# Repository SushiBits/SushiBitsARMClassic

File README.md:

# SushiBits ARM Classic

ARM7TDMI-S in Arduino form factor.

## License

This is open source hardware licensed under [3-clause BSD license](LICENSE.md).

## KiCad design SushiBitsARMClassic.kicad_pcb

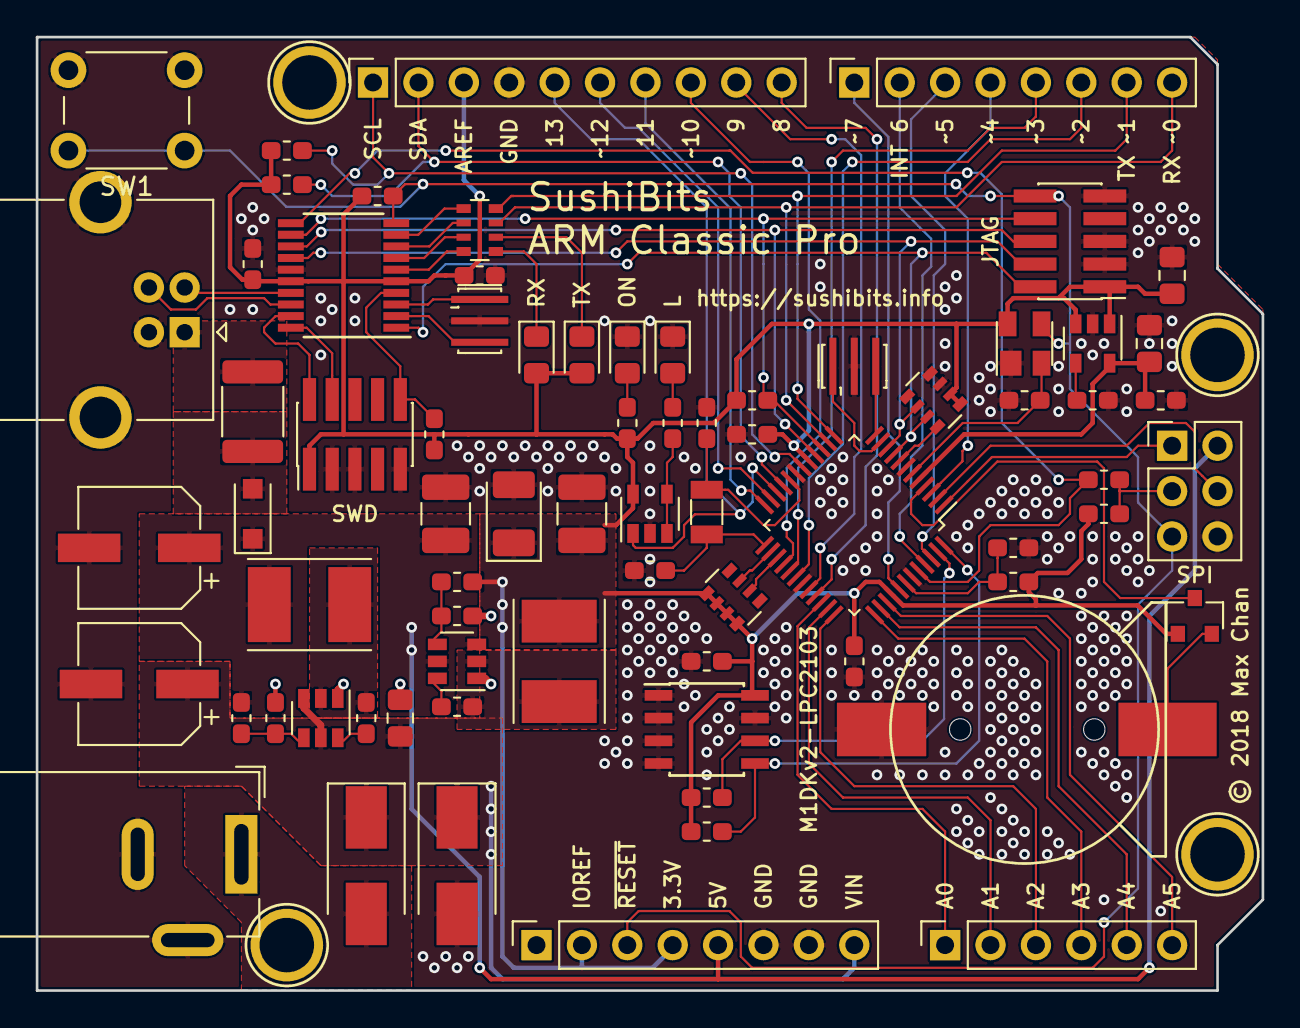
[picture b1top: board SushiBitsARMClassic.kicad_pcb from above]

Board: 2 copper layers, 68.6 x 53.3 mm, 77 parts (0 on the bottom side), 75 nets.

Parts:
BT1: CR1220; Battery_Holder_CR1220
C1, C2, C3, C4, C5, C12, C13, C14, C19, C20: 100n; C_0603_1608Metric_Pad1.05x0.95mm_HandSolder
C6, C7: 3p; C_0603_1608Metric_Pad1.05x0.95mm_HandSolder
C8: 100µ; CP_Elec_6.3x7.7
C9, C11, C15: 10µ; C_0805_2012Metric_Pad1.15x1.40mm_HandSolder
C10: 47µ; C_1210_3225Metric_Pad1.42x2.65mm_HandSolder
C16: 220µ; CP_Elec_6.3x5.3
C17: 220µ; CP_EIA-3528-12_Kemet-T_Pad1.50x2.35mm_HandSolder
C18: 47u; C_1210_3225Metric_Pad1.42x2.65mm_HandSolder
D1: L13; LED_0805_2012Metric_Pad1.15x1.40mm_HandSolder
D2: SK34; D_SMB_Handsoldering
D3: SMBJ15CA; D_SMB_Handsoldering
D4: BAT54C; SOT-23
D5: K34; D_SOD-123F
D6: Power; LED_0805_2012Metric_Pad1.15x1.40mm_HandSolder
D7: RX; LED_0805_2012Metric_Pad1.15x1.40mm_HandSolder
D8: TX; LED_0805_2012Metric_Pad1.15x1.40mm_HandSolder
F1: 1A; Fuse_1812_4532Metric_Pad1.30x3.40mm_HandSolder
J1: SPI; PinHeader_2x03_P2.54mm_Vertical
J2: JTAG; PinHeader_2x05_P1.27mm_Vertical_SMD
J3: DC12V; BarrelJack_Wuerth_6941xx301002
J4: USB_B; USB_B_OST_USB-B1HSxx_Horizontal
J5: Conn_ARM_JTAG_SWD_10; PinHeader_2x05_P1.27mm_Vertical_SMD
L1: 120; L_0603_1608Metric_Pad1.05x0.95mm_HandSolder
L2: 4.7µ; L_Taiyo-Yuden_NR-50xx_HandSoldering
L3: 2.2µ; L_Taiyo-Yuden_NR-50xx_HandSoldering
M1: LPC2103; LQFP-48_7x7mm_P0.5mm
P1: Power; PinSocket_1x08_P2.54mm_Vertical
P2: Analog; PinSocket_1x06_P2.54mm_Vertical
P3: Digital; PinSocket_1x10_P2.54mm_Vertical
P4: Digital; PinSocket_1x08_P2.54mm_Vertical
P5, P6, P7, P8: CONN_01X01; Arduino_1pin
R1, R2, R9, R12, R16: 10k; R_0603_1608Metric_Pad1.05x0.95mm_HandSolder
R3, R4, R5, R6, R8: 4.7k; R_0603_1608Metric_Pad1.05x0.95mm_HandSolder
R7, R15: 510; R_0603_1608Metric_Pad1.05x0.95mm_HandSolder
R10: R; R_0603_1608Metric_Pad1.05x0.95mm_HandSolder
R11: 2k; R_0603_1608Metric_Pad1.05x0.95mm_HandSolder
R13: 11k; R_0603_1608Metric_Pad1.05x0.95mm_HandSolder
R14: 33k; R_0603_1608Metric_Pad1.05x0.95mm_HandSolder
RN1, RN2: 4.7k; R_Array_Convex_4x0603
RN3: 510; R_Array_Convex_4x0603
SW1: RESET; SW_PUSH_6mm
U1: MAX811S; SOT-143
U2: 24LC512; SOIC-8_3.9x4.9mm_P1.27mm
U3: LMV321; SOT-23-5
U4, U5: TPS563200; SOT-23-6
U6: LP2985-1.8; SOT-23-5
U7: STM32F042F4Px; TSSOP-20_4.4x6.5mm_P0.65mm
Y1: 32768; Crystal_SMD_3215-2Pin_3.2x1.5mm
Y2, Y3: 16M; Resonator_SMD_muRata_CSTxExxV-3Pin_3.0x1.1mm_HandSoldering

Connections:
+1V8: C3.1, C15.1, M1.5, U6.5
+3V3: C1.1, C2.1, C5.2, C11.1, C17.1, C18.1, C19.1, C20.1, D4.1, D7.2, D8.2, J2.1, J5.1, L1.2, L3.2, M1.17, M1.40, P1.2, P1.4, P3.3, R1.1, R3.1, R4.1, R5.2, R6.1, R8.1, R9.1, R14.1, R15.1, R16.2, RN1.1, RN1.2, RN1.3, RN1.4, RN2.1, RN2.2, U1.4, U2.8, U3.5, U6.1, U6.3, U7.5, U7.16
+5V: C10.1, C16.1, D5.1, J1.2, L2.2, P1.5, R13.1, U5.3, U5.5
+12V: C8.1, C9.1, D2.1, D3.1, P1.8, U4.3, U4.5
+BATT: D4.3, M1.4
/0(RX): M1.14, P4.8, RN3.3
/1(TX): M1.13, P4.7, RN3.4
/2: M1.30, P4.6
/3: M1.29, P4.5
/4: M1.3, P4.4
/5: M1.46, P4.3
/6: M1.45, P4.2
/7: M1.41, P4.1
/8: M1.33, P3.10
/9: M1.32, P3.9
/10: M1.28, P3.8
/11: M1.24, P3.7
/12: M1.23, P3.6
/13: M1.22, P3.5, U3.1
/A0: M1.34, P2.1
/A1: M1.35, P2.2
/A2: M1.36, P2.3
/A3: M1.37, P2.4
/A4: M1.38, P2.5
/A5: M1.39, P2.6
/BOOT: M1.44, R7.2, U7.11
/CLK1: M1.11, Y2.1
/CLK2: M1.12, Y2.3
/MISO: J1.1, M1.1
/MOSI: J1.4, M1.2
/RTC1: C6.1, M1.20, Y1.1
/RTC2: C7.1, M1.25, Y1.2
/Reset: J1.5, J2.10, P1.3, R1.2, SW1.1, U1.3, U7.10
/SCK: J1.3, R7.1, R9.2
/SCL: M1.18, P3.1, R6.2
/SCL1: M1.47, R4.2, U2.6
/SDA: M1.21, P3.2, R8.2
/SDA1: M1.48, R3.2, U2.5
/TCK: J2.4, M1.10, RN2.6, U7.14
/TDI: J2.8, M1.15, R5.1, U7.12
/TDO: J2.6, M1.16, U7.13
/TMS: J2.2, M1.9, RN2.7, U7.1
/USB Interface/Reset: J5.10, R16.1, U7.4
GND: BT1.2, C1.2, C2.2, C3.2, C4.2, C5.1, C6.2, C7.2, C8.2, C9.2, C10.2, C11.2, C12.2, C15.2, C16.2, C17.2, C18.2, C19.2, C20.2, D1.1, D3.2, D6.1, J1.6, J2.3, J2.5, J2.9, J3.2, J3.3, J4.4, J4.5, J5.3, J5.5, J5.9, M1.7, M1.19, M1.31, M1.43, P1.6, P1.7, P3.4, R2.2, R11.2, R12.2, RN2.3, RN2.4, SW1.2, U1.1, U2.1, U2.2, U2.3, U2.4, U2.7, U3.2, U4.1, U5.1, U6.2, U7.15, Y2.2, Y3.2
unnamed: BT1.1, D4.2
unnamed: C4.1, L1.1, M1.42
unnamed: C12.1, U6.4
unnamed: C13.1, L2.1, U4.2
unnamed: C13.2, U4.6
unnamed: C14.1, L3.1, U5.2
unnamed: C14.2, U5.6
unnamed: D1.2, R10.2
unnamed: D2.2, J3.1
unnamed: D6.2, R15.2
unnamed: D7.1, RN3.2
unnamed: D8.1, RN3.1
unnamed: F1.2, J4.1
unnamed: J4.2, U7.17
unnamed: J4.3, U7.18
unnamed: J5.2, U7.19
unnamed: J5.4, U7.20
unnamed: M1.6, R2.1, U1.2
unnamed: M1.8, RN2.8
unnamed: M1.26, RN1.7
unnamed: M1.27, RN1.6
unnamed: R10.1, U3.3, U3.4
unnamed: R11.1, R13.2, U4.4
unnamed: R12.1, R14.2, U5.4
unnamed: RN3.5, U7.9
unnamed: RN3.6, U7.8
unnamed: RN3.7, U7.7
unnamed: RN3.8, U7.6
unnamed: U7.2, Y3.3
unnamed: U7.3, Y3.1
VBUS: D5.2, F1.1

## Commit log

2018-08-28 Code dump: finished v1 PCB
2018-08-28 Added page foot notes
2018-08-28 Added page foot notes 2
2018-09-16 Rework: improving power delivery

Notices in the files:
SushiBitsARMClassic.kicad_pcb:
© 2018 Max Chan
